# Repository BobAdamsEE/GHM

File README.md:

# GHM

This repository contains files that attempt to clone parts of the Google
Home Mini smart home assistant. The final intention is to have the 
ability to make custom designs that re-use the housing and speaker of
the original.

## Goals

* Clone Input PCBA (Design DONE, Fit test TODO)
* Document constraints of main PCBA (clearance, LED placement)
* Document speaker parameters
* Create open source main PCBA with TBD features

## Input PCBA

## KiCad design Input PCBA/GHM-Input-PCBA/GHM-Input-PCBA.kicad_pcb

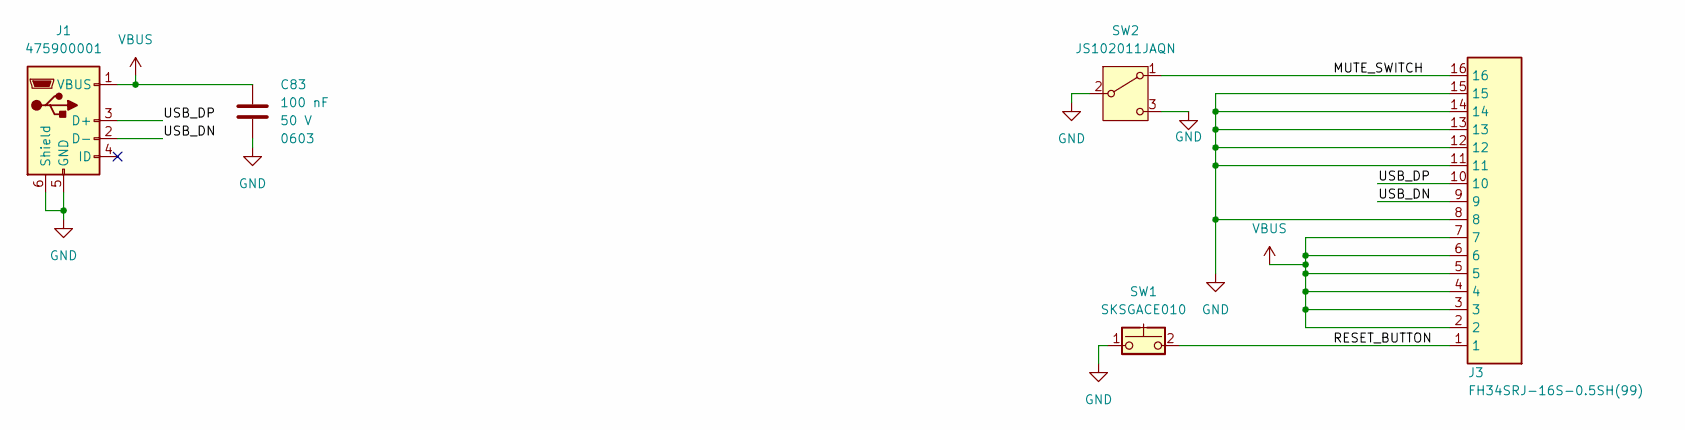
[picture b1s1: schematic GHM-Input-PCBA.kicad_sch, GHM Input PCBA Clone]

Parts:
C83: 100 nF; C_0603_1608Metric; Voltage Rating 50 V; MPN CGA3E2X7R1H104K080AA
J1: 475900001; MOLEX_475900001; MPN 475900001
J3: FH34SRJ-16S-0.5SH(99); HIROSE_FH34SRJ-16S-0.5SH(99); MPN FH34SRJ-16S-0.5SH(99)
SW1: SKSGACE010; ALPSALPINE_SKSGACE010; MPN SKSGACE010
SW2: JS102011JAQN; C&K_JS102011JAQN; MPN JS102011JAQN

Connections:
/MUTE_SWITCH: J3.16, SW2.1 (A)
/RESET_BUTTON: J3.1, SW1.2, SW1.4 (2)
/USB_DN: J1.2 (D-), J3.9
/USB_DP: J1.3 (D+), J3.10
GND: C83.1, J1.5 (GND), J1.6 (Shield), J3.8, J3.11, J3.12, J3.13, J3.14, J3.15, SW1.1, SW1.3 (1), SW2.2 (B), SW2.3 (C)
VBUS: C83.2, J1.1 (VBUS), J3.2, J3.3, J3.4, J3.5, J3.6, J3.7

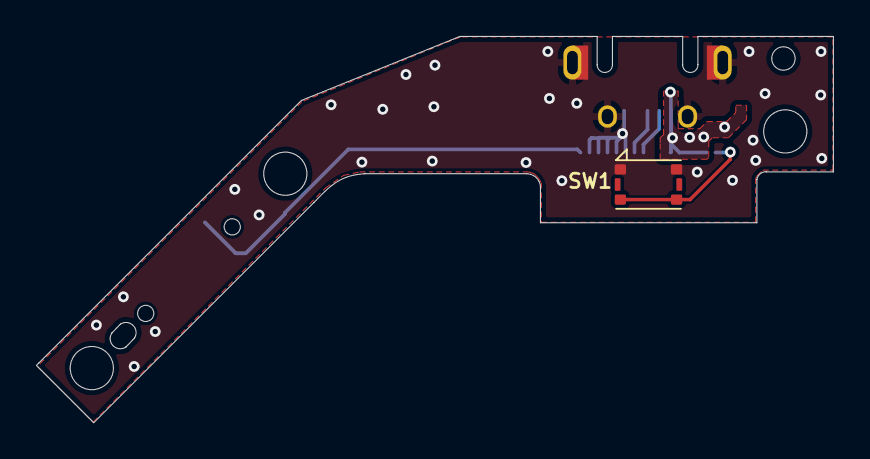
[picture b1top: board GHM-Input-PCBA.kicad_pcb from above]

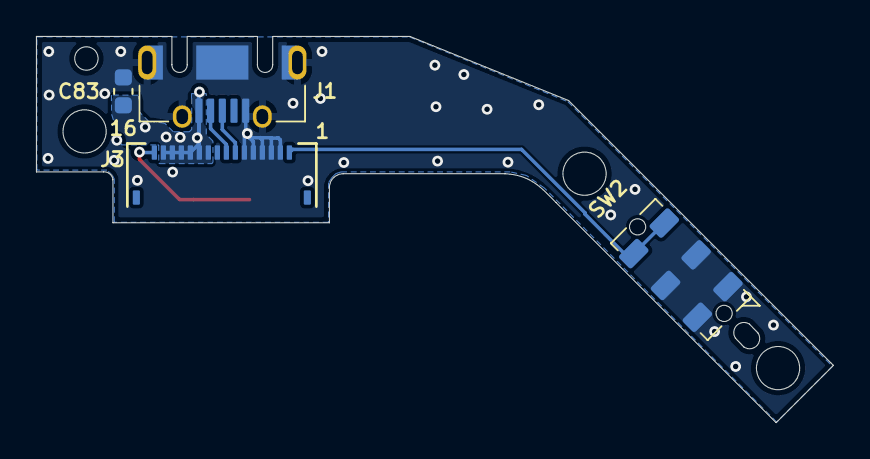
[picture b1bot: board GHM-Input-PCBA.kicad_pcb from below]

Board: 2 copper layers, 44.3 x 21.5 mm, 5 parts (4 on the bottom side), 6 nets.

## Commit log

2025-03-09 Initial Release
2025-04-27 Scehmatic & BOM Added
